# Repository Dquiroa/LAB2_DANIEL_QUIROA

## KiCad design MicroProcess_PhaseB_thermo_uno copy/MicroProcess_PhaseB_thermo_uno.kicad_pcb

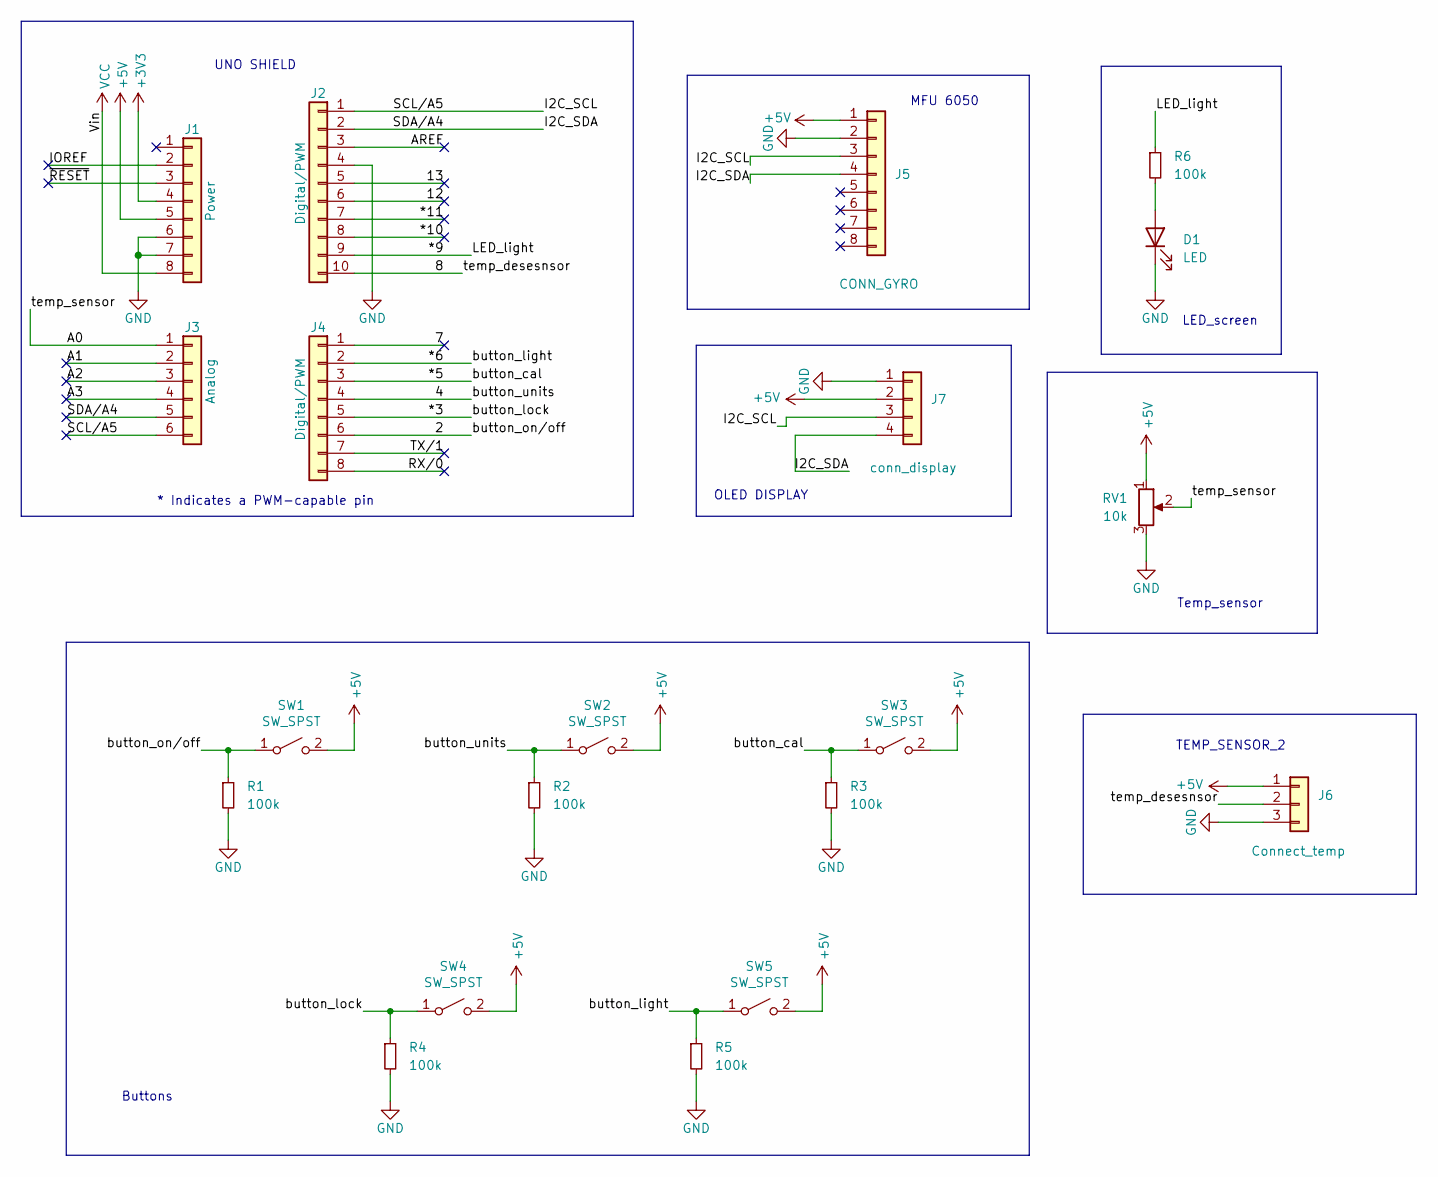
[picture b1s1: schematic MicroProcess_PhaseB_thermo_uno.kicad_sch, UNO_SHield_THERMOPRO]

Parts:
D1: LED; LED_D5.0mm
J1: Power; PinSocket_1x08_P2.54mm_Vertical
J2: Digital/PWM; PinSocket_1x10_P2.54mm_Vertical
J3: Analog; PinSocket_1x06_P2.54mm_Vertical
J4: Digital/PWM; PinSocket_1x08_P2.54mm_Vertical
J5: CONN_GYRO; PinSocket_1x08_P2.54mm_Vertical
J6: Connect_temp; JST_XH_B3B-XH-AM_1x03_P2.50mm_Vertical
J7: conn_display; PinSocket_1x04_P2.54mm_Vertical
R1, R2, R3, R4, R5, R6: 100k; R_Axial_DIN0207_L6.3mm_D2.5mm_P10.16mm_Horizontal
RV1: 10k; Potentiometer_Bourns_3386P_Vertical
SW1, SW2, SW3, SW4, SW5: SW_SPST; SW_PUSH_6mm

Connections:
+3V3: J1.4
+5V: J1.5, J5.1, J6.1, J7.2, RV1.1, SW1.2 (B), SW2.2 (B), SW3.2 (B), SW4.2 (B), SW5.2 (B)
/2: J4.6, R1.1, SW1.1 (A)
/4: J4.4, R2.1, SW2.1 (A)
/7: J4.1
/8: J2.10, J6.2
/12: J2.6
/13: J2.5
/*3: J4.5, R4.1, SW4.1 (A)
/*5: J4.3, R3.1, SW3.1 (A)
/*6: J4.2, R5.1, SW5.1 (A)
/*9: J2.9, R6.1
/*10: J2.8
/*11: J2.7
/A0: J3.1, RV1.2
/A1: J3.2
/A2: J3.3
/A3: J3.4
/AREF: J2.3
/I2C_SCL: J2.1, J3.6, J5.3, J7.3
/I2C_SDA: J2.2, J3.5, J5.4, J7.4
/IOREF: J1.2
/RX/0: J4.8
/TX/1: J4.7
/~RESET: J1.3
GND: D1.1 (K), J1.6, J1.7, J2.4, J5.2, J6.3, J7.1, R1.2, R2.2, R3.2, R4.2, R5.2, RV1.3
unnamed: D1.2 (A), R6.2
VCC: J1.8

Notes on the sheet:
LED_screen
UNO SHIELD
OLED DISPLAY
Temp_sensor
TEMP_SENSOR_2
* Indicates a PWM-capable pin
MFU 6050
Buttons

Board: 2 copper layers, 20 parts (0 on the bottom side), 13 nets, no tracks yet.

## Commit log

2025-01-24 Create LAB2_MICRO_Q1.ino
    Question 1
2025-01-24 Create LAB2_MICRO_Q2.ino
    Question 2
2025-01-24 Create LAB2_MICRO_Q3.ino
    Question 3
2025-01-24 Create LAB2_MICRO_Q4.ino
    Question 4
2025-01-31 kicad
2025-01-31 lab 3
2025-01-31 block disgram
2025-02-03 phase b
2025-02-04 phase b gerber
2025-02-05 Update Daniel_Quiroa.zip
    updated files for the PCB
2025-02-26 lab 4 code
2025-02-26 final code for Phase C
2025-03-05 lab4
    lab 4 re upload - original code in gerber files same come just different location
2025-03-13 micro_phase D
2025-03-13 Phase D Research
